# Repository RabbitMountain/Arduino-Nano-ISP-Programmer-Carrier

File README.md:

(Rabbit Mountain Research) AVR Arduino Pro Micro & Arduino Pro Mini ISP programmers
========================

This shield / carrier board, once assembled, turns your Arduino Nano, <S>Arduino Pro Mini, or Arduino Pro Micro</S> into an AVR ISP programmer. The ISCP socket is wired to work directly with the ArduinoISP code.

This board was designed to replace my old legacy TinyISP programmer from Adafruit (which no longer works easily with Ubuntu Linux). I would like a newer AVR ISP programmer that works without installing drivers AND has a more modern USB-micro or USB-C port. The Pro Mini version can be used with the new Sparkfun Serial Basic with USB-C (or any FTDI compatible Cable).

Currently I am having trouble getting the pro mini and pro micro versions to work. New tests on the protype pcbs are in progress. Might be a resistor problem or a grounding pin issue like the Nano version had.

<B>Update Nov-24-2021:</B> First Prtotype programmer using a USB-C Nano + Nano AVR ISP Programming Shield / Carrier Board was a success! Status LEDs, power jumper for target AVR, and everything seems to work. Was a minor error with the ISP pinout not being grounded, but fixing that fixed this version of the programmer. It also was able to reflash the arduino bootloader to an Arduino Mega 2560 (an old Rambo-Mini). My old Adafruit / Sparkfun TinyISP programmer was never able to program the 2560 AVR. Woo!!

Planning on putting together my first commercial run of PCBs for a small assembly of units for purchase. Please check Tindie / RabbitMountainResearch.com for more info on how to buy those if you are interested.

Repository Contents
-------------------
* **/Hardware** - All Eagle design files (.brd, .sch)
* **/Code** - Arduino *.Ino sketch file

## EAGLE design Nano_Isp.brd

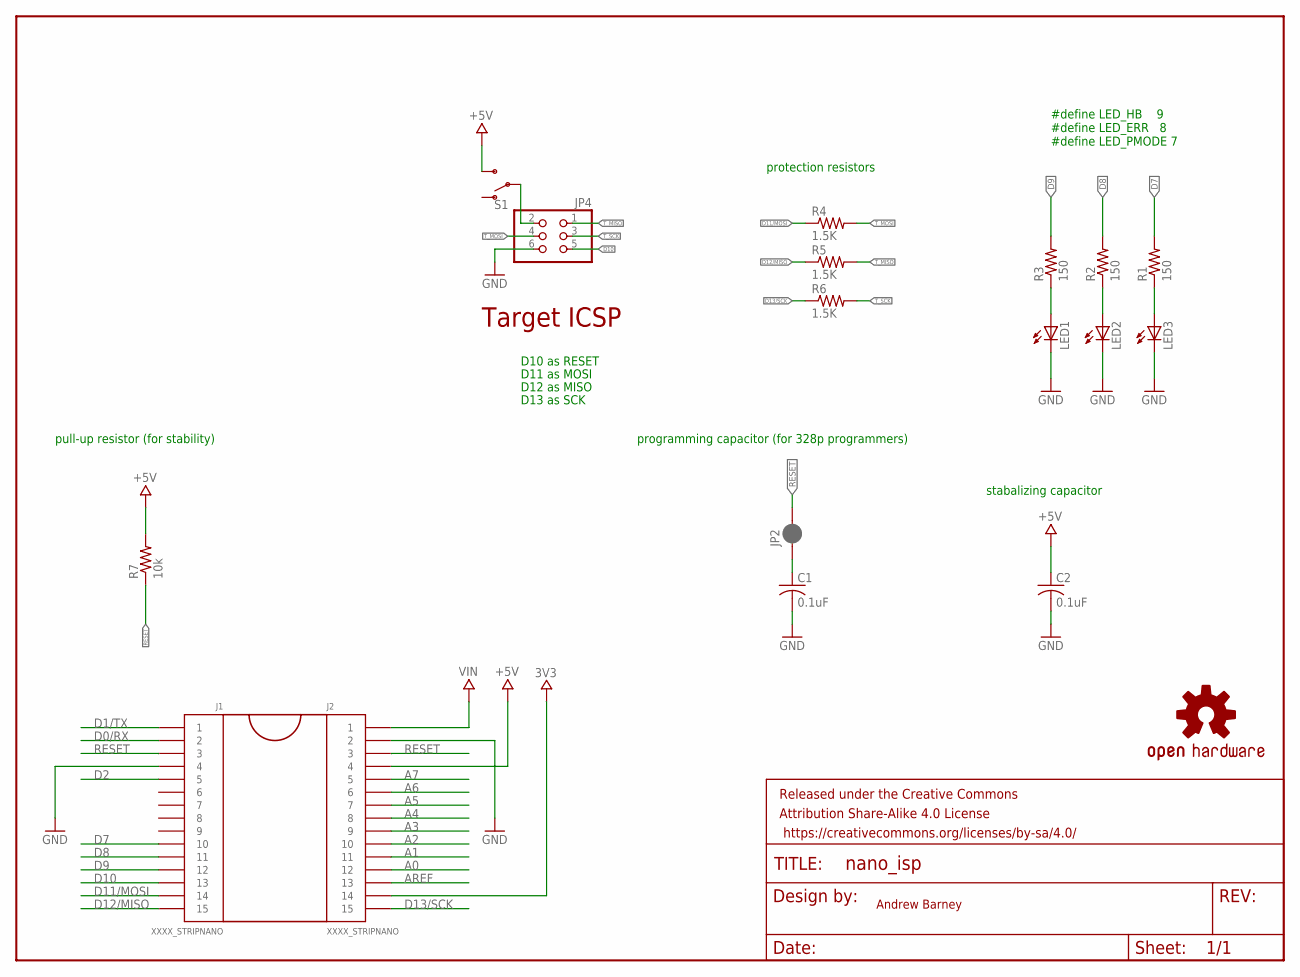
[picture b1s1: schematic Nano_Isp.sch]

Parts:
C1, C2: 0.1uF; C0805
FRAME1: FRAME-LETTERNO_PACKAGE; DUMMY
J1, J2: XXXX_STRIPNANO; HEAD15-NOSS
JP2: JUMPER-SMT_2_NC_PASTE_SILK; SMT-JUMPER_2_NC_PASTE_SILK
JP4: PINHD-2X3; 2X03
LED1, LED2, LED3: LEDCHIP-LED0805; CHIP-LED0805
R1, R2, R3: 150; R0805
R4, R5, R6: 1.5K; R0805
R7: 10k; R0805
S1: SWITCH-SPDT-SMD-AYZ0202; SWITCH_DPDT_SMD_AYZ0202
U$9: OSHW-LOGOS; OSHW-LOGO-S

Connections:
3V3: J2.14
+5V: C2.1, J2.4, R7.2, S1.3 (S)
A0: J2.12
A1: J2.11
A2: J2.10
A3: J2.9
A4: J2.8
A5: J2.7
A6: J2.6
A7: J2.5
AREF: J2.13
D0/RX: J1.2
D1/TX: J1.1
D2: J1.5
D7: J1.10, R1.2
D8: J1.11, R2.2
D9: J1.12, R3.2
D10: J1.13, JP4.5
D11/MOSI: J1.14, R4.1
D12/MISO: J1.15, R5.1
D13/SCK: J2.15, R6.1
GND: C1.2, C2.2, J1.4, J2.2, JP4.6, LED1.C, LED2.C, LED3.C
unnamed: LED3.A, R1.1
unnamed: LED2.A, R2.1
unnamed: LED1.A, R3.1
unnamed: C1.1, JP2.1
RESET: J1.3, J2.3, JP2.2, R7.1
T_MISO: JP4.1, R5.2
T_MOSI: JP4.4, R4.2
T_SCK: JP4.3, R6.2
VCC2: JP4.2, S1.2
VIN: J2.1

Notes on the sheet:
Andrew Barney
D10 as RESET
D11 as MOSI
D12 as MISO
D13 as SCK
#define LED_HB 9 #define LED_ERR 8 #define LED_PMODE 7
protection resistors
Target ICSP
pull-up resistor (for stability)
programming capacitor (for 328p programmers)
stabalizing capacitor

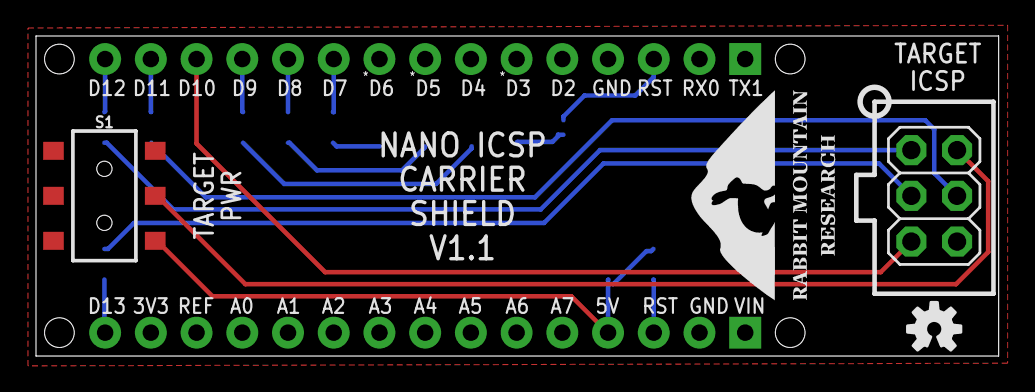
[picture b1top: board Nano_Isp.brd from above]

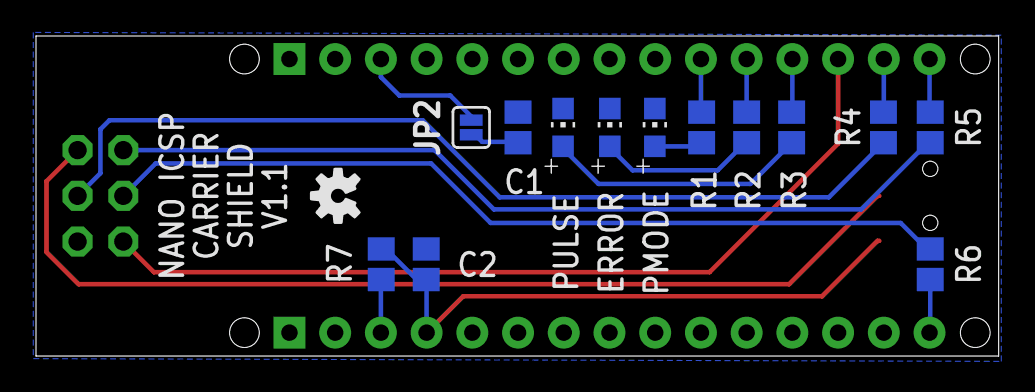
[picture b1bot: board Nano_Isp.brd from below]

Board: 2 copper layers, 53.5 x 17.8 mm, 21 parts (14 on the bottom side), 18 nets.

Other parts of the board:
U$1: RMR-SIT-8MM
U$2: OSHW-LOGOS; OSHW-LOGO-S

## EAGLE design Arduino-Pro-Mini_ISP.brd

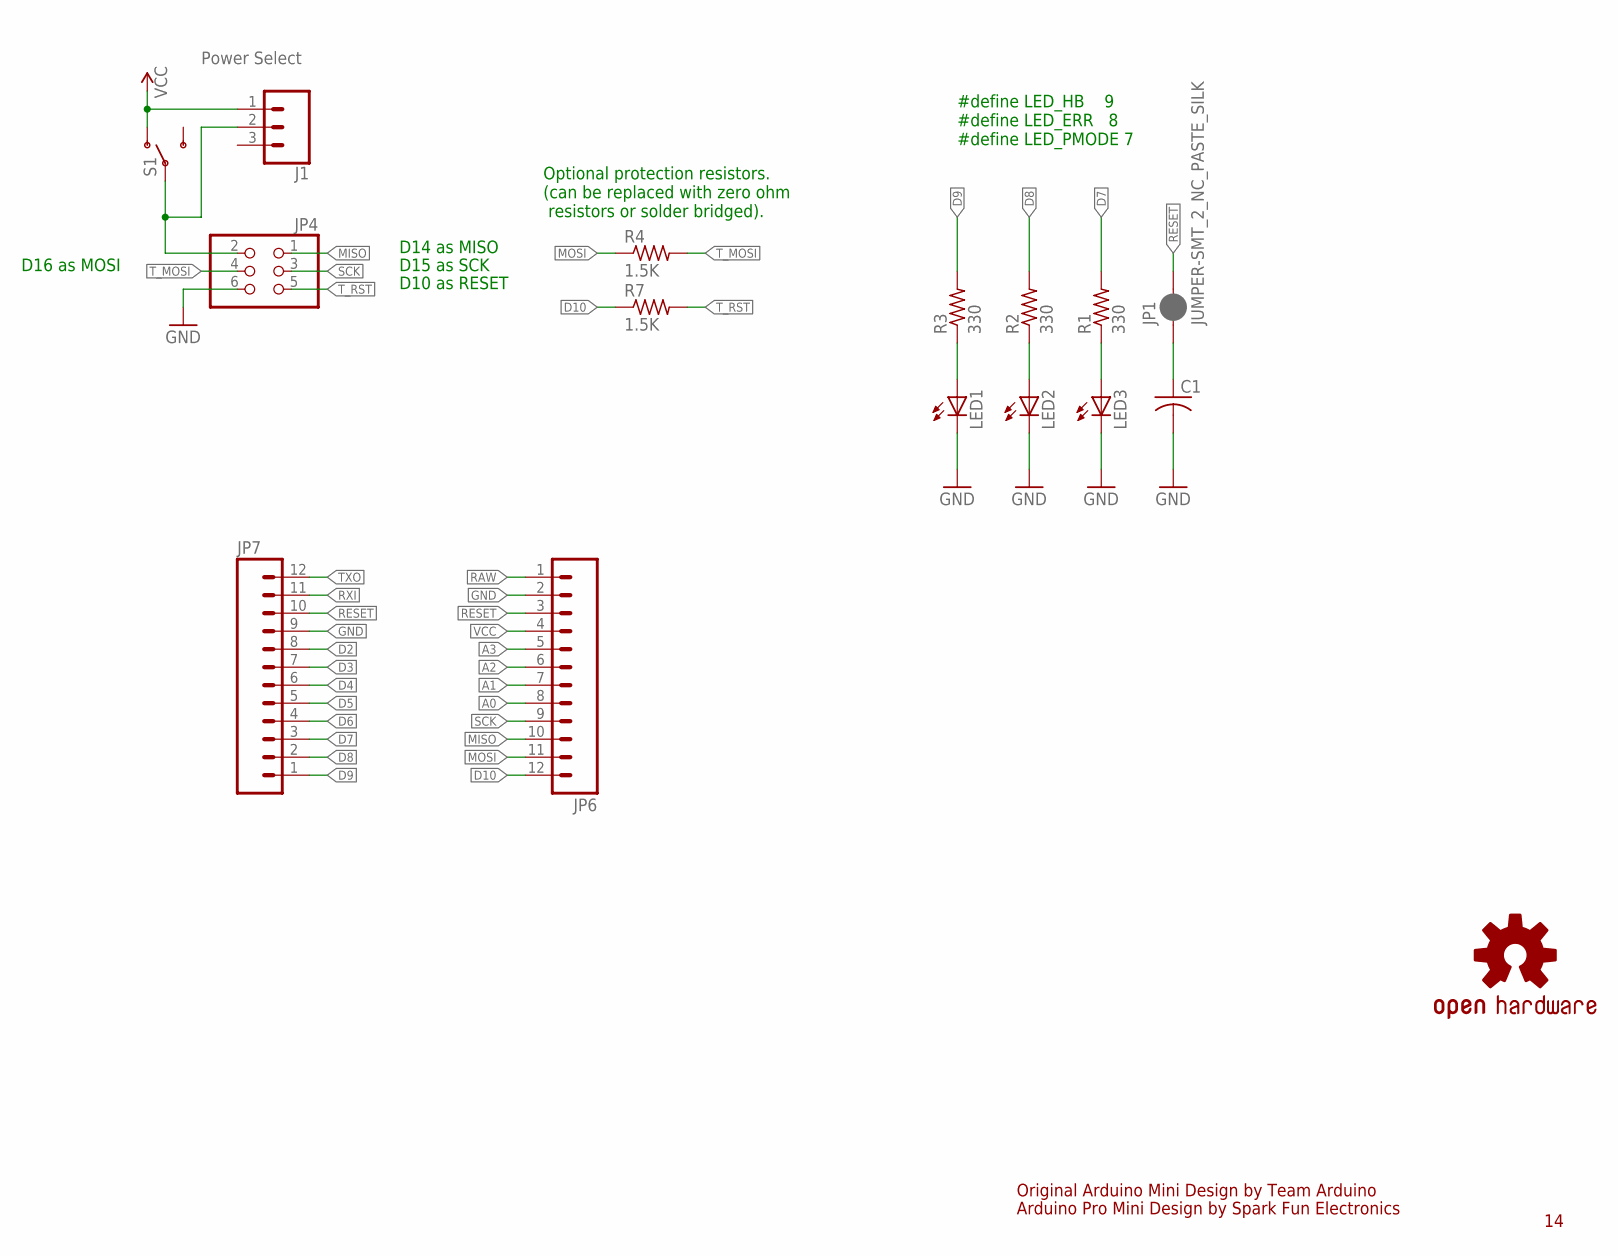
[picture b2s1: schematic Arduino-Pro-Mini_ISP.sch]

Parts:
C1: C-USC0805; C0805
J1: CONN_03; 1X03
JP1: JUMPER-SMT_2_NC_PASTE_SILK; SMT-JUMPER_2_NC_PASTE_SILK
JP4: PINHD-2X3; 2X03
JP6, JP7: M12PTH; 1X12
LED1, LED2, LED3: LEDCHIP-LED0805; CHIP-LED0805
R1, R2, R3: 330; R0805
R4, R7: 1.5K; R0805
S1: Power Select; AYZ0202
U$3: OSHW-LOGOS; OSHW-LOGO-S

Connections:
A0: JP6.8
A1: JP6.7
A2: JP6.6
A3: JP6.5
D2: JP7.8
D3: JP7.7
D4: JP7.6
D5: JP7.5
D6: JP7.4
D7: JP7.3, R1.2
D8: JP7.2, R2.2
D9: JP7.1, R3.2
D10: JP6.12, R7.1
GND: C1.2, JP4.6, JP6.2, JP7.9, LED1.C, LED2.C, LED3.C
MISO: JP4.1, JP6.10
MOSI: JP6.11, R4.1
unnamed: LED3.A, R1.1
unnamed: LED2.A, R2.1
unnamed: LED1.A, R3.1
unnamed: C1.1, JP1.1
RAW: JP6.1
RESET: JP1.2, JP6.3, JP7.10
RXI: JP7.11
SCK: JP4.3, JP6.9
TXO: JP7.12
T_MOSI: JP4.4, R4.2
T_RST: JP4.5, R7.2
VCC: J1.1, JP6.4, S1.1 (O)
VCC2: J1.2, JP4.2, S1.2

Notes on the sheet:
Original Arduino Mini Design by Team Arduino
Arduino Pro Mini Design by Spark Fun Electronics
D10 as RESET
D16 as MOSI
D14 as MISO
D15 as SCK
#define LED_HB 9 #define LED_ERR 8 #define LED_PMODE 7
Optional protection resistors. (can be replaced with zero ohm resistors or solder bridged).

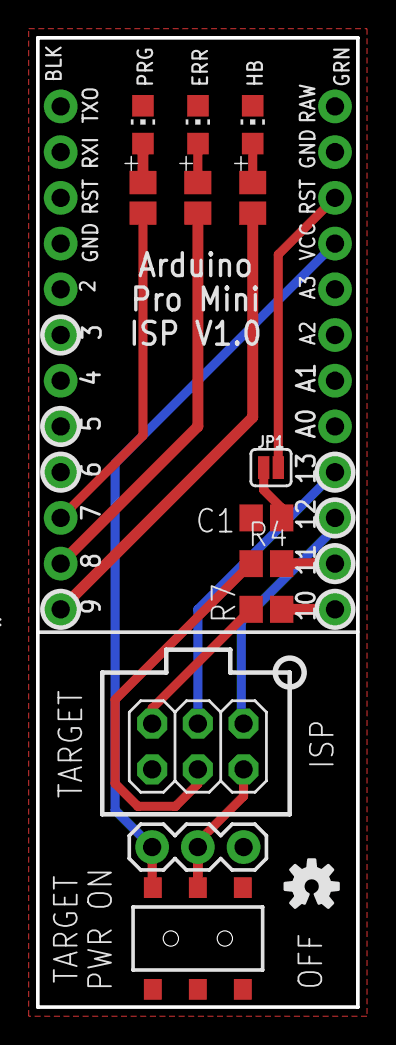
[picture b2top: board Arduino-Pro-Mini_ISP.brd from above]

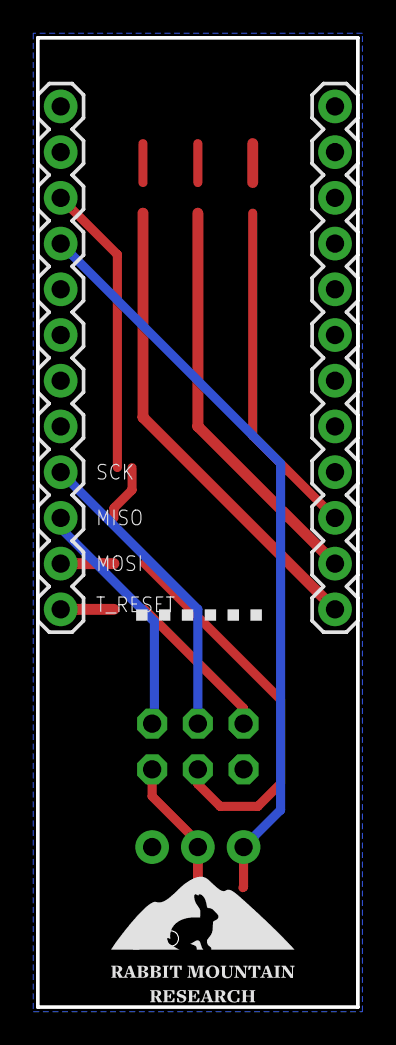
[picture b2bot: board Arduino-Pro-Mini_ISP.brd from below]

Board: 2 copper layers, 17.8 x 53.8 mm, 17 parts (3 on the bottom side), 17 nets.

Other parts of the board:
U$1: RMR-SIT-7MM

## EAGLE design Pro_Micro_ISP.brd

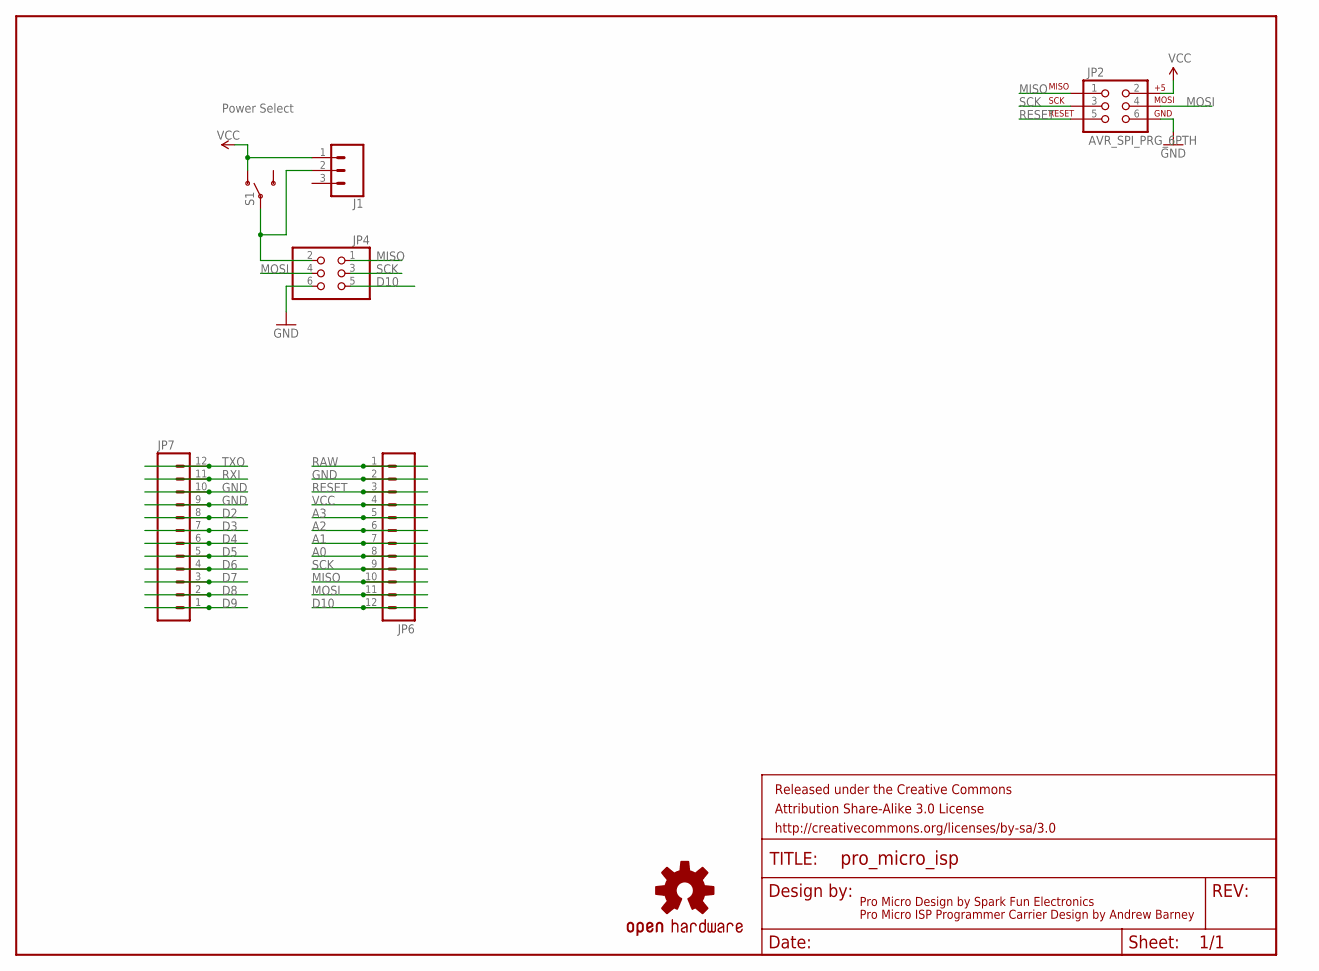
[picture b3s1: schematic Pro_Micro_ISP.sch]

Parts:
FRAME1: FRAME-LETTER; CREATIVE_COMMONS
J1: CONN_03; 1X03
JP2: AVR_SPI_PRG_6PTH; 2X3
JP4: PINHD-2X3; 2X03
JP6, JP7: M12PTH; 1X12
S1: Power Select; AYZ0202
U$3: OSHW-LOGOS; OSHW-LOGO-S

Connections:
A0: JP6.8
A1: JP6.7
A2: JP6.6
A3: JP6.5
D2: JP7.8
D3: JP7.7
D4: JP7.6
D5: JP7.5
D6: JP7.4
D7: JP7.3
D8: JP7.2
D9: JP7.1
D10: JP4.5, JP6.12
GND: JP2.6, JP4.6, JP6.2, JP7.9, JP7.10
MISO: JP2.1, JP4.1, JP6.10
MOSI: JP2.4, JP4.4, JP6.11
unnamed: J1.2, JP4.2, S1.2
RAW: JP6.1
RESET: JP2.5, JP6.3
RXI: JP7.11
SCK: JP2.3, JP4.3, JP6.9
TXO: JP7.12
VCC: J1.1, JP2.2, JP6.4, S1.1 (O)

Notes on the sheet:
Pro Micro Design by Spark Fun Electronics
Pro Micro ISP Programmer Carrier Design by Andrew Barney

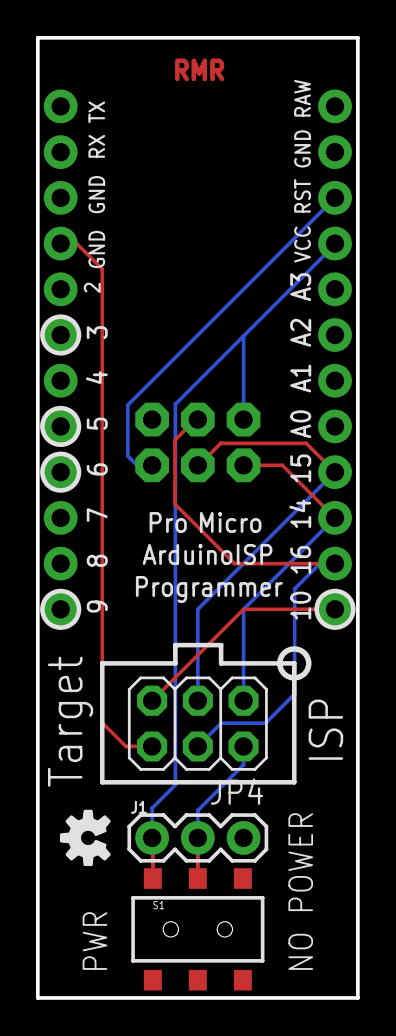
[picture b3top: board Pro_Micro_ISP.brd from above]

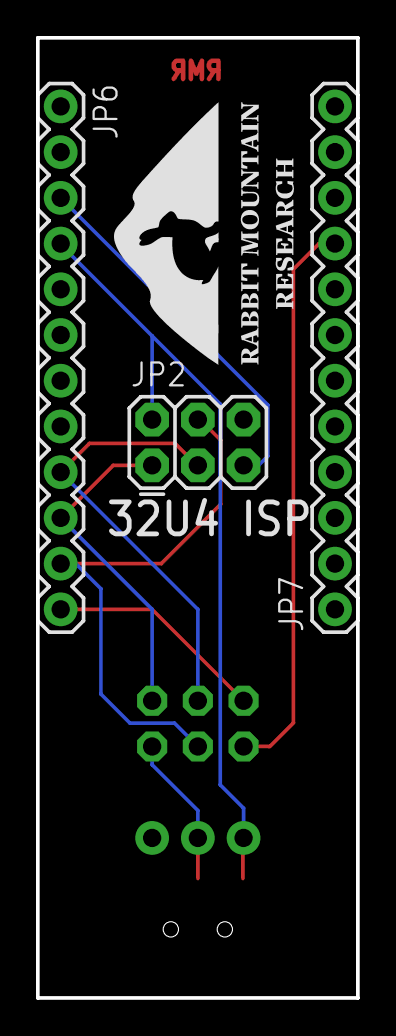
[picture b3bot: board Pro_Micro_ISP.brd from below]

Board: 2 copper layers, 17.8 x 53.3 mm, 9 parts (4 on the bottom side), 8 nets.

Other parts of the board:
U$1: RMR-SIT-10MM

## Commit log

2020-12-19 Add files via upload
    A carrier / shield for the Arduinuso compatible Sparkfun Pro Micro for ISP Programming AVR chips. A more modern ISP programmer to the now dated Adafruit's USBTinyISP and Sparkfun's Pocket AVR Program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
2020-12-19 Add files via upload
    Fixed missing traces to SMD switch. Minor changes to silkscreen.
2021-11-25 Add files via upload
    Renamed Files. Remapped resistors and capacitors and silkscreen changes to V1.1 before ordering potential first commercial PCB run.

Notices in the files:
parts and their libraries:
SparkFun-Connectors: Licensing: Creative Commons ShareAlike 4.0 International - https://creativecommons.org/licenses/by-sa/4.0
SparkFun-Aesthetics: Released under the Creative Commons Attribution Share-Alike 4.0 License
SparkFun-Aesthetics: https://creativecommons.org/licenses/by-sa/4.0
